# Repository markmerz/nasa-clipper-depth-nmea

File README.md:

# nasa-clipper-depth-nmea
NMEA0183 converter to NASA Clipper Depth sounder.

An affordable depth sounder, the "NASA Clipper Depth" does not have NMEA0183 output.
It has an I2C output for driving a secondary display. This project taps into
I2C output, decodes display driving protocol, creates NMEA0103 messages from
it and sends them over USB-SERIAL link for distributing with other devices.

This project is heavily inspired by https://wiki.openseamap.org/wiki/De:NASA_Clipper_Range

As of 28.06.2024, the PCB part of the project is in its final form. Arduino code is partial,
lacking actual decoding and recoding parts. I intend to install the device to the boat
and observe the actual protocol on the wire, as I feel this protocol is slightly
different between device versions.

PCB is designed to fit into a sealed plastic box I had lying around. Unfortunately, I don't
remember when and from where I got the box, so I can't provide a reference for where you could get
the same enclosure. The box measures 11.3 x 8.9 x 5.5 centimetres, made from hard grey plastic.

PCB cost about 11€ delivered into the EU, ordered from jlcpcb.com. Manufacturer
website also handles taxes and customs. DIN5 connectors were ~15€, arduino-compatible board was 
~5€, the enclosure was probably ~10€, and the rest of the parts were jellybeans from the box.

My point is that when you don't particularly like tinkering with electronics, it may be 
wiser to buy an echosounder that already has NMEA0183 or even NMEA2000 output. But when you like 
building things, this project is an excellent way to save costs, although it requires You to pay 
a little more.

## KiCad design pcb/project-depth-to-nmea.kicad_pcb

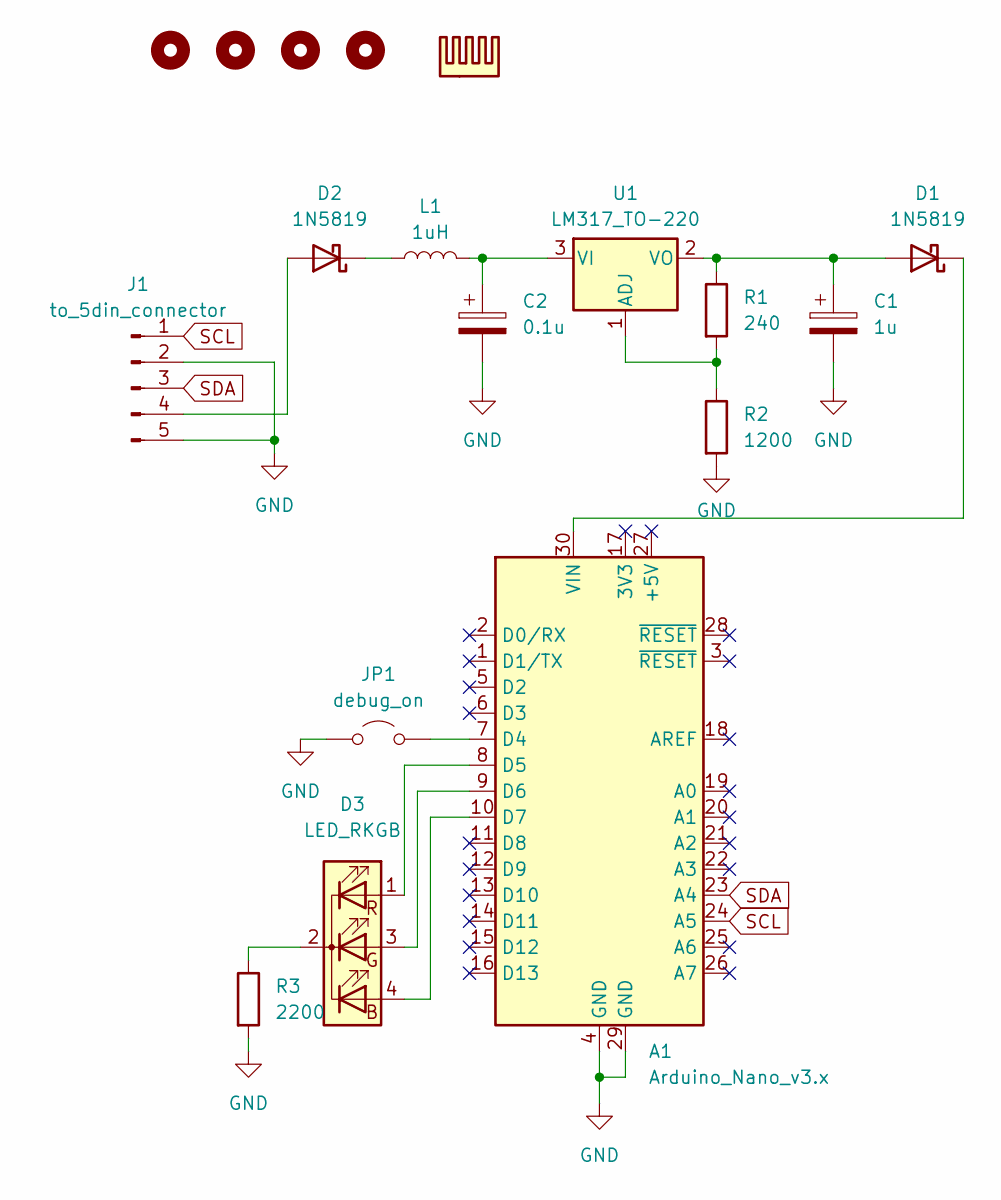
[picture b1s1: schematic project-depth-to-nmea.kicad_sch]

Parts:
A1: Arduino_Nano_v3.x; Arduino_Nano
C1: 1u; CP_Radial_D5.0mm_P2.50mm
C2: 0.1u; CP_Radial_D5.0mm_P2.50mm
D1, D2: 1N5819; D_DO-41_SOD81_P2.54mm_Vertical_AnodeUp
D3: LED_RKGB; LED_D5.0mm-4_RGB_Wide_Pins
H1, H2, H3, H4: MountingHole; MountingHole_3.2mm_M3
HS1: Heatsink; Heatsink_Stonecold_HS-S02_13.21x9.53mm
J1: to_5din_connector; PinSocket_1x05_P2.54mm_Vertical
JP1: debug_on; TestPoint_2Pads_Pitch2.54mm_Drill0.8mm
L1: 1uH; L_Axial_L9.5mm_D4.0mm_P2.54mm_Vertical_Fastron_SMCC
R1: 240; R_Axial_DIN0207_L6.3mm_D2.5mm_P2.54mm_Vertical
R2: 1200; R_Axial_DIN0207_L6.3mm_D2.5mm_P2.54mm_Vertical
R3: 2200; R_Axial_DIN0207_L6.3mm_D2.5mm_P2.54mm_Vertical
U1: LM317_TO-220; TO-220-3_Vertical

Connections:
GND: A1.4 (GND), A1.29 (GND), C1.2, C2.2, J1.2, J1.5, JP1.1 (A), R2.2, R3.2
unnamed: A1.7 (D4), JP1.2 (B)
unnamed: A1.8 (D5), D3.1 (RA)
unnamed: A1.9 (D6), D3.3 (GA)
unnamed: A1.10 (D7), D3.4 (BA)
unnamed: A1.30 (VIN), D1.1 (K)
unnamed: C1.1, D1.2 (A), R1.1, U1.2 (VO)
unnamed: D2.2 (A), J1.4
unnamed: D2.1 (K), L1.1
unnamed: D3.2 (K), R3.1
unnamed: R1.2, R2.1, U1.1 (ADJ)
unnamed: C2.1, L1.2, U1.3 (VI)
SCL: A1.24 (A5), J1.1
SDA: A1.23 (A4), J1.3

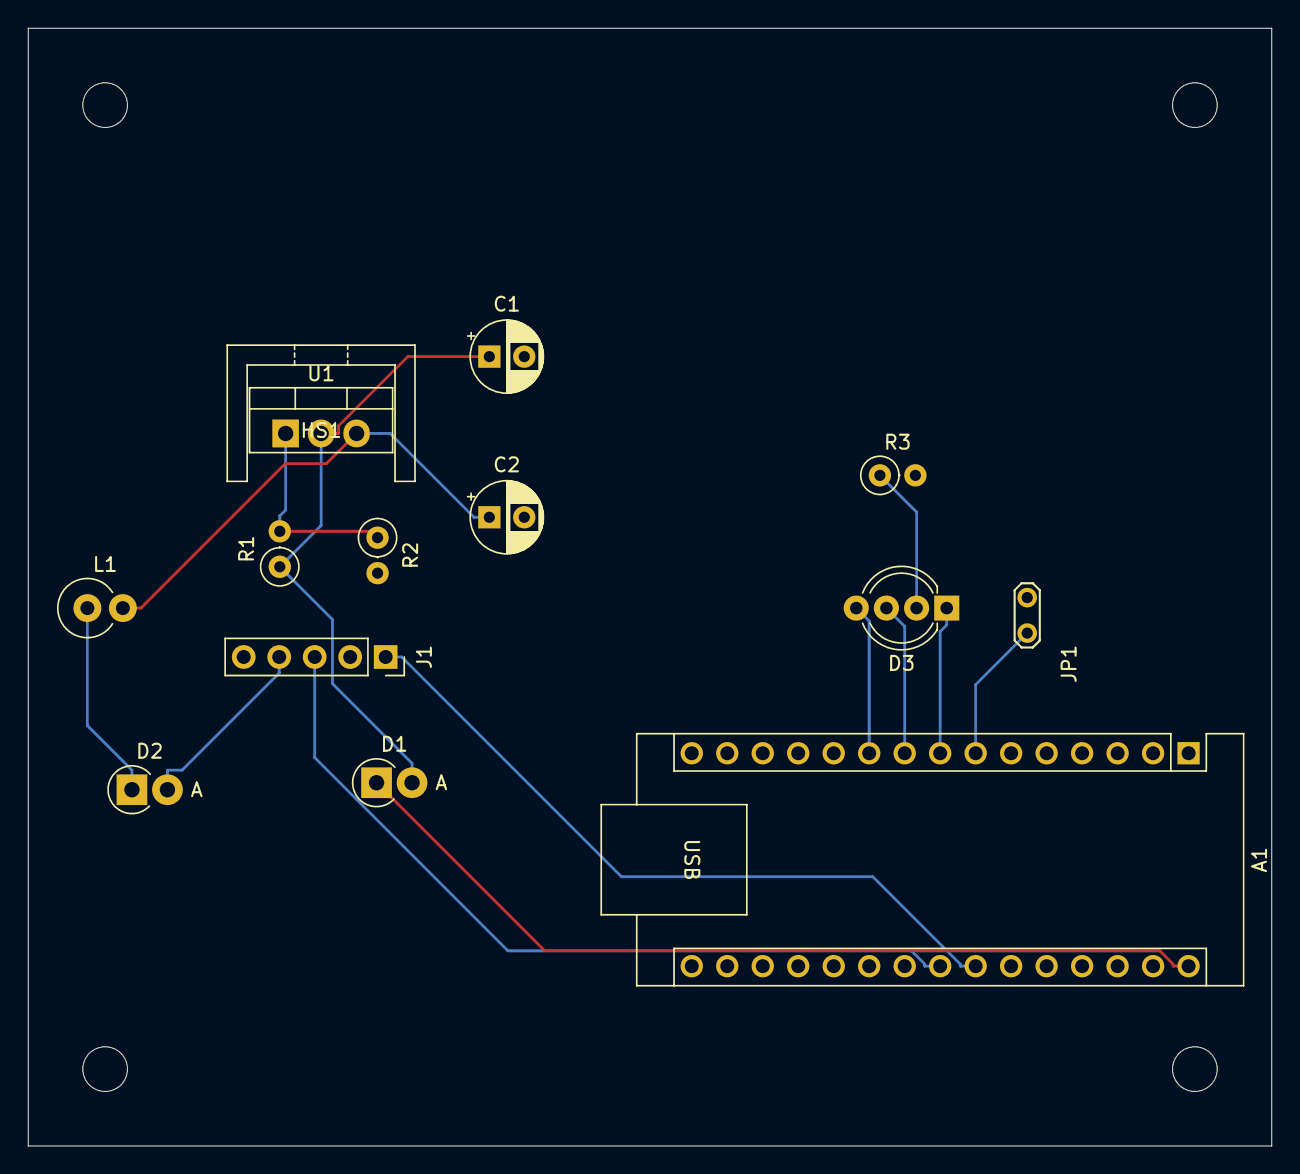
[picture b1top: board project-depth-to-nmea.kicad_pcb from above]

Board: 2 copper layers, 89.0 x 80.0 mm, 18 parts (0 on the bottom side), 14 nets.

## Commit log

2024-06-28 Initial import
2025-04-19 Logic works with hacked-together simulator. Not tested with actual unit.
2025-04-20 Make some hardcoded values explicit
